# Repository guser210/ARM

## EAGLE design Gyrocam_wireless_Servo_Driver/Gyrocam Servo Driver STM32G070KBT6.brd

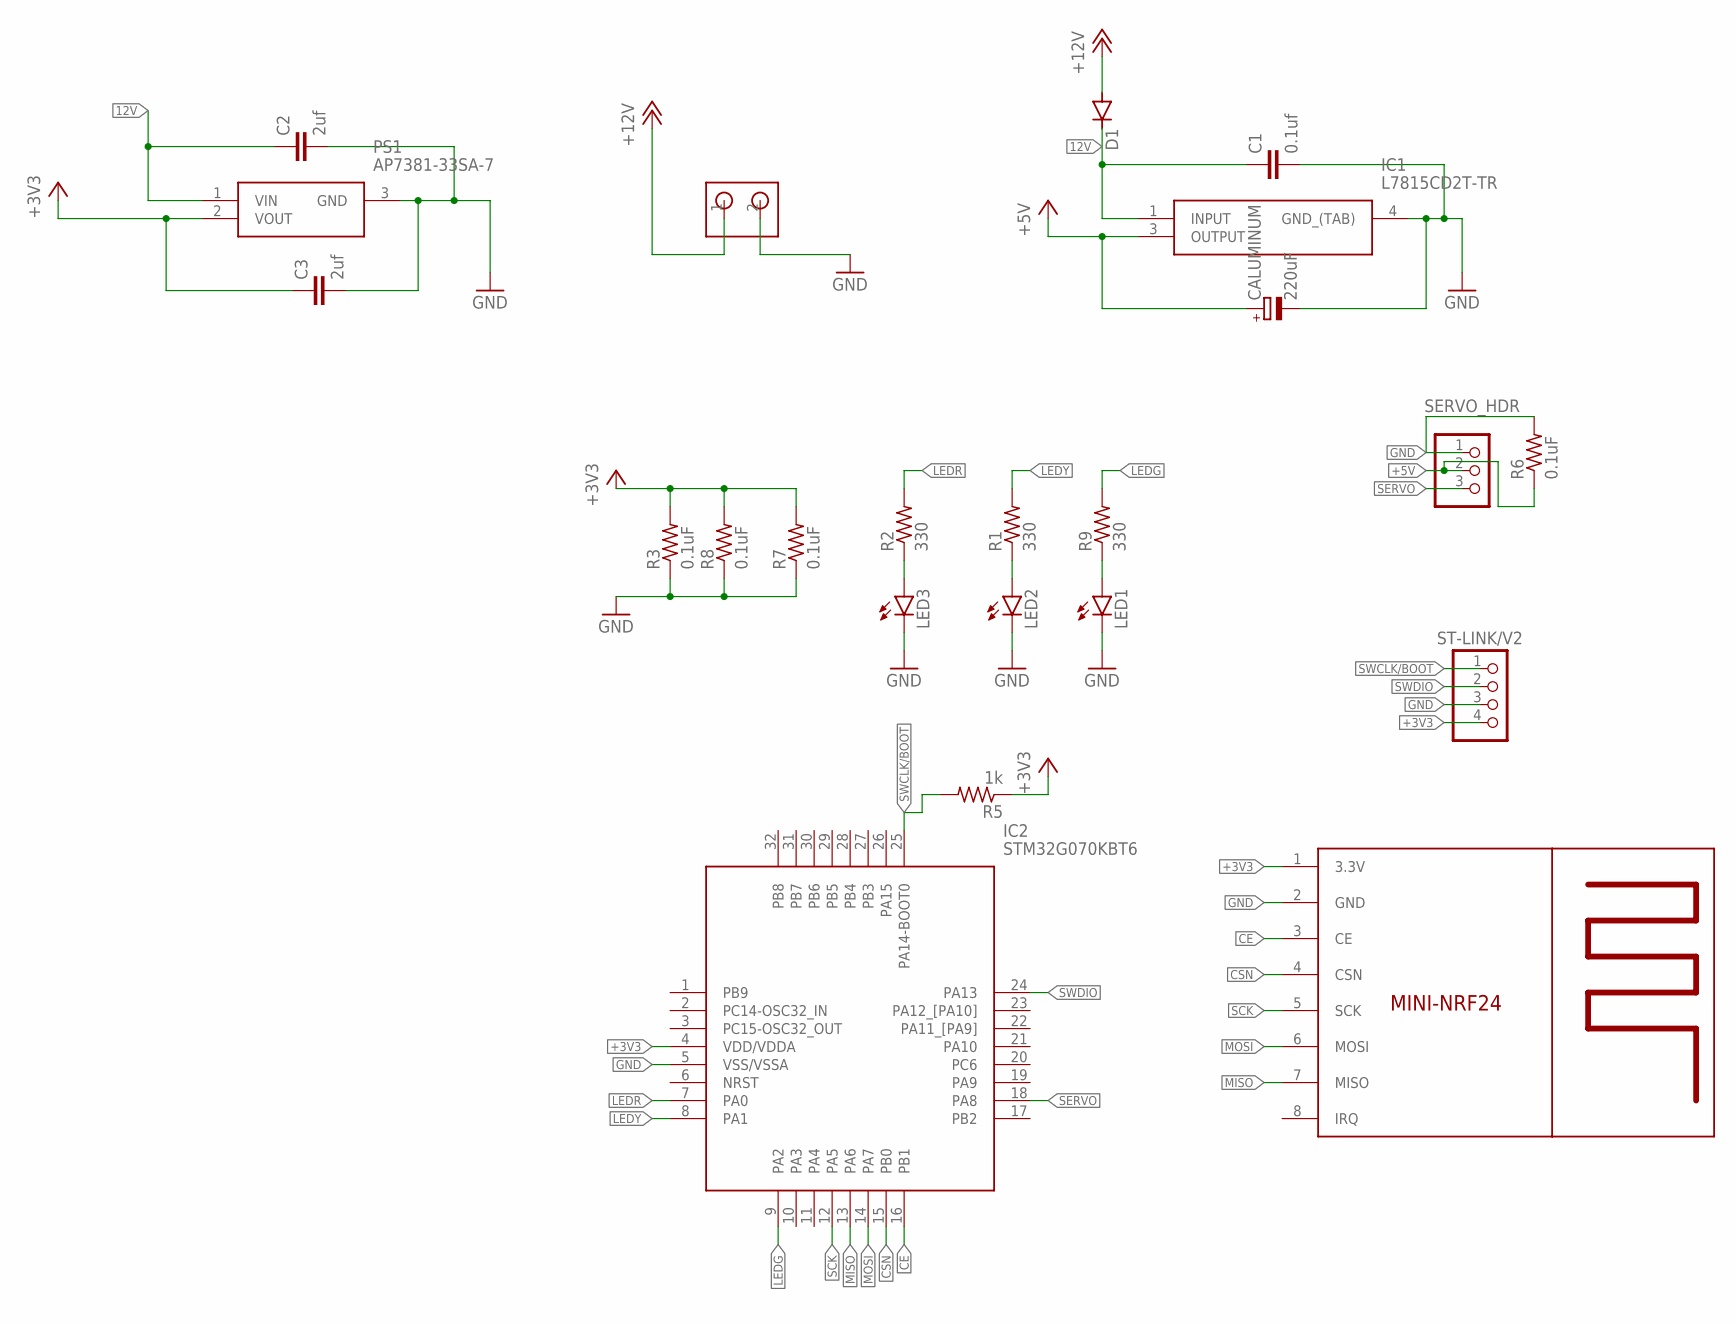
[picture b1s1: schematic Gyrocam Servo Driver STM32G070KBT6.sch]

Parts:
C1: 0.1uf; C0805K
C2, C3: 2uf; C0805K
CALUMINUM: 220uF; 153CLV-0810
D1: DIODE-DO-214AC; DO-214AC
IC1: L7815CD2T-TR; TO254P1542X460-3N
IC2: STM32G070KBT6; QFP80P900X900X160-32N
LED1, LED2, LED3: LEDSML0805; SML0805
PS1: AP7381-33SA-7; SOT96P240X120-3N
R1, R2, R9: 330; R0805
R3, R6, R7, R8: 0.1uF; R0805
R5: 1k; R0805
SERVO_HDR: PINHD-1X3; 1X03
ST-LINK/V2: PINHD-1X4; 1X04
U$2: MINI-NRF24L01PSMD; NRF24L01_SMD
U$5: PINHEAD2_18AAWG; PINHEAD2_18AWG

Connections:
12V: C1.1, C2.1, D1.C, IC1.1 (INPUT), PS1.1 (VIN)
+3V3: C3.1, IC2.4 (VDD/VDDA), PS1.2 (VOUT), R3.2, R5.1, R7.2, R8.2, ST-LINK/V2.4, U$2.1 (3.3V)
+5V: CALUMINUM.+, IC1.3 (OUTPUT), R6.1, SERVO_HDR.2
+12V: D1.A, U$5.1
CE: IC2.16 (PB1), U$2.3 (CE)
CSN: IC2.15 (PB0), U$2.4 (CSN)
GND: C1.2, C2.2, C3.2, CALUMINUM.-, IC1.4 (GND_(TAB)), IC2.5 (VSS/VSSA), LED1.C, LED2.C, LED3.C, PS1.3 (GND), R3.1, R6.2, R7.1, R8.1, SERVO_HDR.1, ST-LINK/V2.3, U$2.2 (GND), U$5.2
LEDG: IC2.9 (PA2), R9.2
LEDR: IC2.7 (PA0), R2.2
LEDY: IC2.8 (PA1), R1.2
MISO: IC2.13 (PA6), U$2.7 (MISO)
MOSI: IC2.14 (PA7), U$2.6 (MOSI)
unnamed: LED2.A, R1.1
unnamed: LED3.A, R2.1
unnamed: LED1.A, R9.1
SCK: IC2.12 (PA5), U$2.5 (SCK)
SERVO: IC2.18 (PA8), SERVO_HDR.3
SWCLK/BOOT: IC2.25 (PA14-BOOT0), R5.2, ST-LINK/V2.1
SWDIO: IC2.24 (PA13), ST-LINK/V2.2

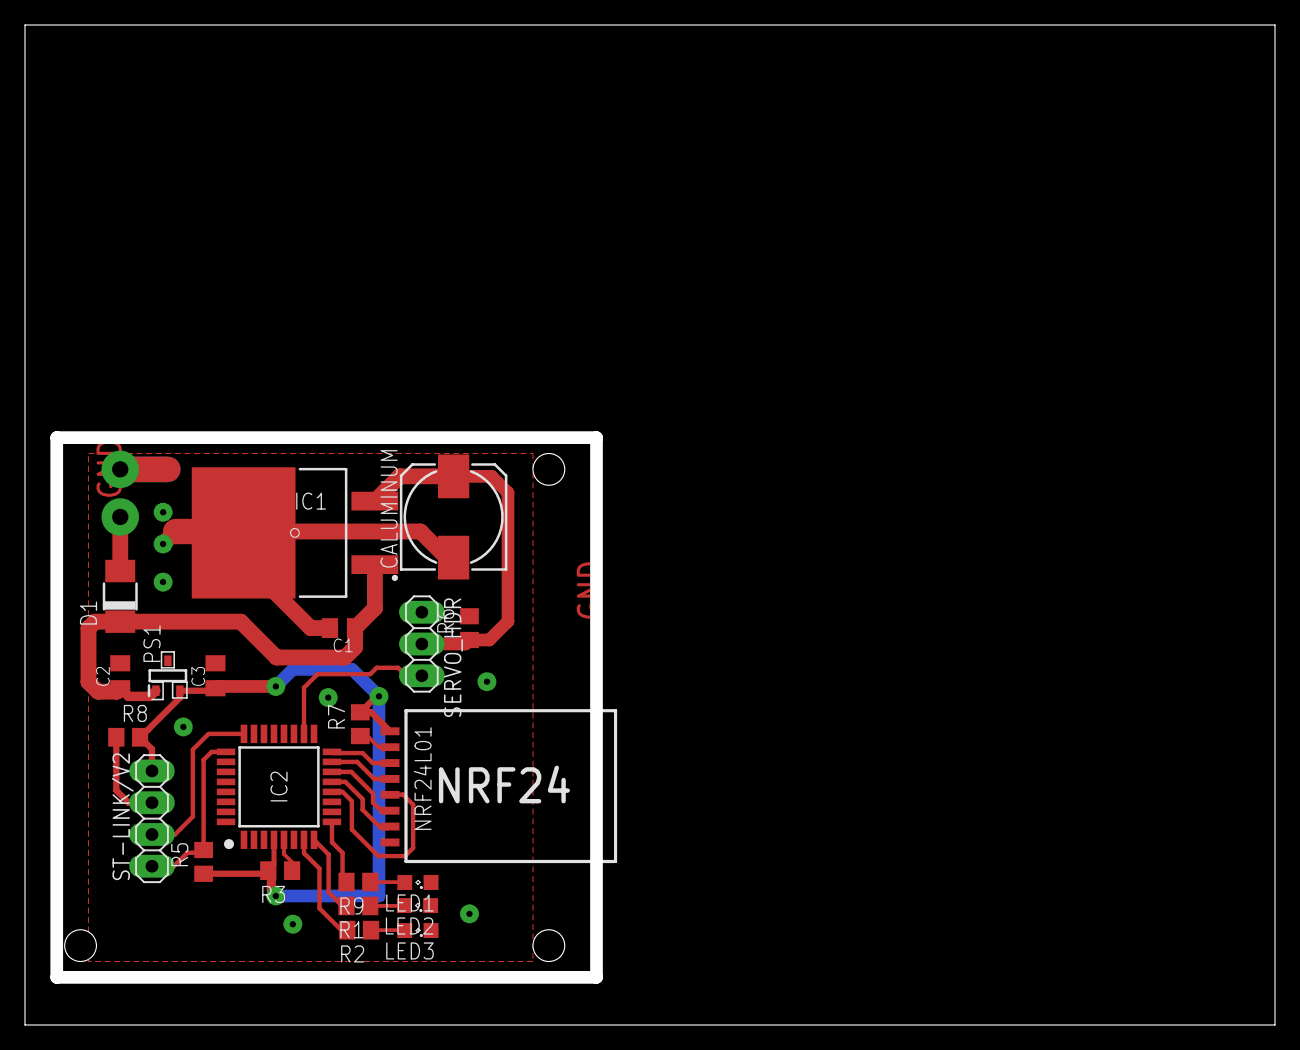
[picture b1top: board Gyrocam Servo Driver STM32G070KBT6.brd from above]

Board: 2 copper layers, 99.0 x 79.0 mm, 23 parts (0 on the bottom side), 19 nets.

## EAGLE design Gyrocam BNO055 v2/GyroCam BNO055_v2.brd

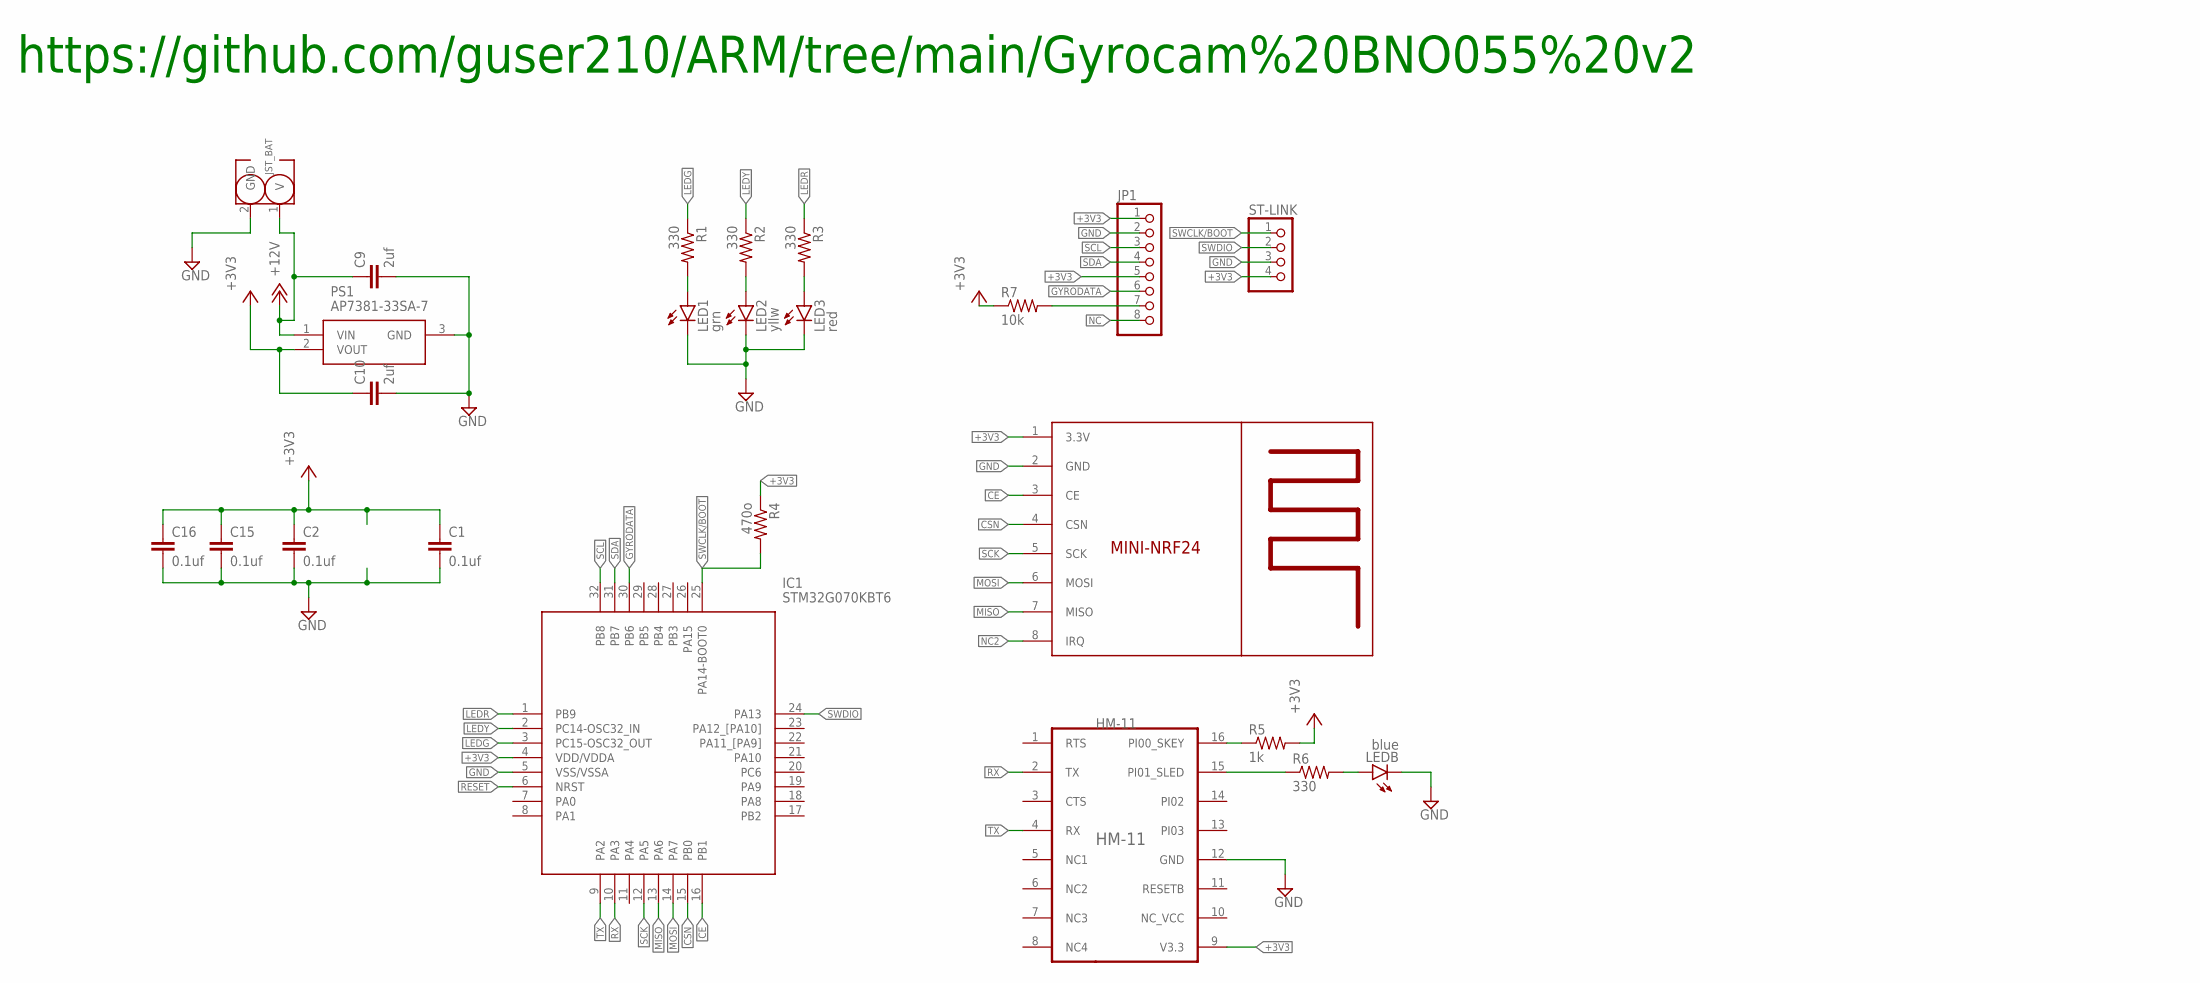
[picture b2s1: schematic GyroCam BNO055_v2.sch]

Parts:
C1: 0.1uf; C0603K
C2, C15, C16: 0.1uf; C0805K
C9, C10: 2uf; C0805K
IC1: STM32G070KBT6; QFP80P900X900X160-32N
JP1: PINHD-1X8; 1X08
LED1: grn; SML0805
LED2: yllw; SML0805
LED3: red; SML0805
LEDB: blue; SML0805
PS1: AP7381-33SA-7; SOT96P240X120-3N
R1, R2, R3, R6: 330; M0805
R4: 470o; M0805
R5: 1k; M0805
R7: 10k; M0805
ST-LINK: PINHD-1X4; 1X04
SUPP: JST2.0MM_2PIN
U$1: HM-11
U$3: NRF24; NRF24L01_SMD

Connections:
+3V3: C1.1, C2.1, C10.1, C15.1, C16.1, IC1.4 (VDD/VDDA), JP1.1, JP1.5, PS1.2 (VOUT), R4.1, R5.2, R7.1, ST-LINK.4, U$1.9 (V3.3), U$3.1 (3.3V)
+12V: C9.1, PS1.1 (VIN), SUPP.1 (V)
BOOT: JP1.7, R7.2
CE: IC1.16 (PB1), U$3.3 (CE)
CSN: IC1.15 (PB0), U$3.4 (CSN)
GND: C1.2, C2.2, C9.2, C10.2, C15.2, C16.2, IC1.5 (VSS/VSSA), JP1.2, LED1.C, LED2.C, LED3.C, LEDB.C, PS1.3 (GND), ST-LINK.3, SUPP.2 (GND), U$1.12 (GND), U$3.2 (GND)
GYRODATA: IC1.30 (PB6), JP1.6
LEDG: IC1.3 (PC15-OSC32_OUT), R1.1
LEDR: IC1.1 (PB9), R3.1
LEDY: IC1.2 (PC14-OSC32_IN), R2.1
MISO: IC1.13 (PA6), U$3.7 (MISO)
MOSI: IC1.14 (PA7), U$3.6 (MOSI)
unnamed: LED2.A, R2.2
unnamed: LED1.A, R1.2
unnamed: LED3.A, R3.2
unnamed: R5.1, U$1.16 (PI00_SKEY)
unnamed: R6.1, U$1.15 (PI01_SLED)
unnamed: LEDB.A, R6.2
NC: JP1.8
NC2: U$3.8 (IRQ)
RESET: IC1.6 (NRST)
RX: IC1.10 (PA3), U$1.2 (TX)
SCK: IC1.12 (PA5), U$3.5 (SCK)
SCL: IC1.32 (PB8), JP1.3
SDA: IC1.31 (PB7), JP1.4
SWCLK/BOOT: IC1.25 (PA14-BOOT0), R4.2, ST-LINK.1
SWDIO: IC1.24 (PA13), ST-LINK.2
TX: IC1.9 (PA2), U$1.4 (RX)

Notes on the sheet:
https://github.com/guser210/ARM/tree/main/Gyrocam%20BNO055%20v2

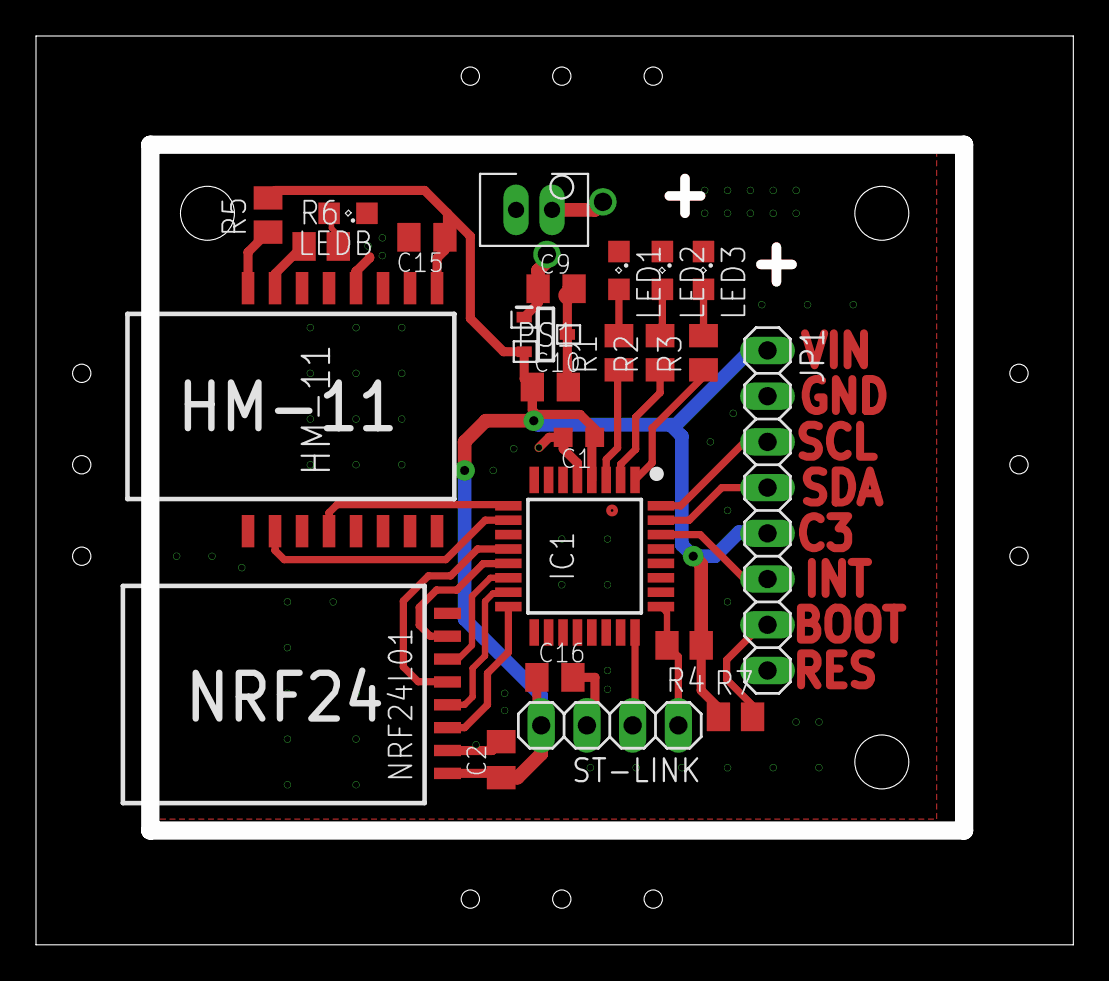
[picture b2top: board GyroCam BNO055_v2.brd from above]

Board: 2 copper layers, 56.6 x 49.5 mm, 24 parts (0 on the bottom side), 25 nets.

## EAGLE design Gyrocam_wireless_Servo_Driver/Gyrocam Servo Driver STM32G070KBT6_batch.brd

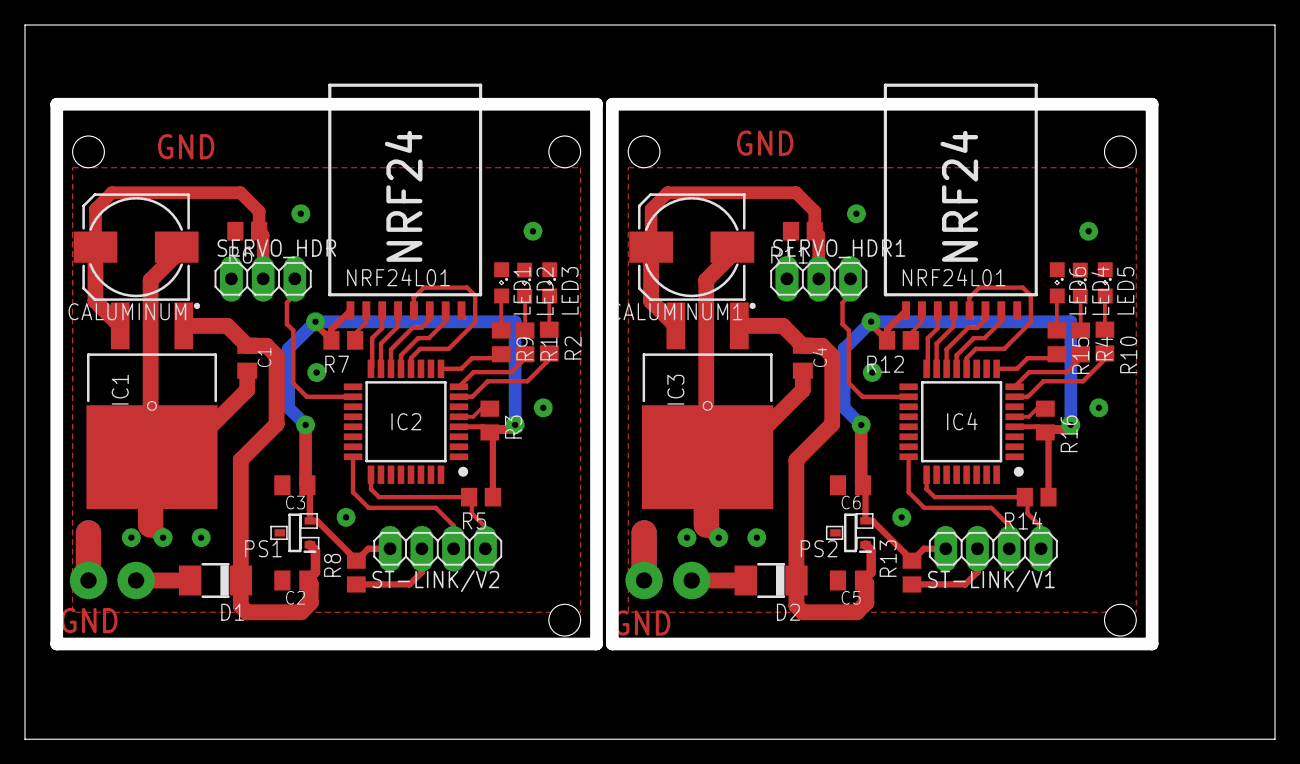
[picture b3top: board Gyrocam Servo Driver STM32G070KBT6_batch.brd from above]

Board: 2 copper layers, 99.0 x 56.1 mm, 46 parts (0 on the bottom side), 38 nets.

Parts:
C1, C4: 0.1uf; C0805K
C2, C3, C5, C6: 2uf; C0805K
CALUMINUM, CALUMINUM1: 220uF; 153CLV-0810
D1, D2: DIODE; DO-214AC
IC1, IC3: L7815CD2T-TR; TO254P1542X460-3N
IC2, IC4: STM32G070KBT6; QFP80P900X900X160-32N
LED1, LED6: LEDG; SML0805
LED2, LED4: LEDY; SML0805
LED3, LED5: LEDR; SML0805
PS1, PS2: AP7381-33SA-7; SOT96P240X120-3N
R1, R2, R4, R9, R10, R15: 330; R0805
R3, R7, R12, R16: .1uF; R0805
R5, R14: 1k; R0805
R6, R8, R11, R13: 0.1uF; R0805
SERVO_HDR, SERVO_HDR1: 1X03
ST-LINK/V1, ST-LINK/V2: 1X04
U$1, U$2: NRF24L01; NRF24L01_SMD
U$3, U$5: PINHEAD2_18AAWG; PINHEAD2_18AWG

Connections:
12V: C1.1, C2.1, D1.C, IC1.1, PS1.1
12V1: C4.1, C5.1, D2.C, IC3.1, PS2.1
+3V1: C6.1, IC4.4, PS2.2, R12.2, R13.2, R14.1, R16.2, ST-LINK/V1.4, U$1.1
+3V3: C3.1, IC2.4, PS1.2, R3.2, R5.1, R7.2, R8.2, ST-LINK/V2.4, U$2.1
+5V: CALUMINUM.+, IC1.3, R6.1, SERVO_HDR.2
+5V1: CALUMINUM1.+, IC3.3, R11.1, SERVO_HDR1.2
+12V: D1.A, U$5.1
+12V1: D2.A, U$3.1
CE: IC2.16, U$2.3
CE1: IC4.16, U$1.3
CSN: IC2.15, U$2.4
CSN1: IC4.15, U$1.4
GND: C1.2, C2.2, C3.2, CALUMINUM.-, IC1.4, IC2.5, LED1.C, LED2.C, LED3.C, PS1.3, R3.1, R6.2, R7.1, R8.1, SERVO_HDR.1, ST-LINK/V2.3, U$2.2, U$5.2
GND1: C4.2, C5.2, C6.2, CALUMINUM1.-, IC3.4, IC4.5, LED4.C, LED5.C, LED6.C, PS2.3, R11.2, R12.1, R13.1, R16.1, SERVO_HDR1.1, ST-LINK/V1.3, U$1.2, U$3.2
LEDG: IC2.9, R9.2
LEDG1: IC4.9, R15.2
LEDR: IC2.7, R2.2
LEDR1: IC4.7, R10.2
LEDY: IC2.8, R1.2
LEDY1: IC4.8, R4.2
MISO: IC2.13, U$2.7
MISO1: IC4.13, U$1.7
MOSI: IC2.14, U$2.6
MOSI1: IC4.14, U$1.6
unnamed: LED2.A, R1.1
unnamed: LED3.A, R2.1
unnamed: LED1.A, R9.1
unnamed: LED4.A, R4.1
unnamed: LED5.A, R10.1
unnamed: LED6.A, R15.1
SCK: IC2.12, U$2.5
SCK1: IC4.12, U$1.5
SERVO: IC2.18, SERVO_HDR.3
SERVO1: IC4.18, SERVO_HDR1.3
SWCLK/BOOT: IC2.25, R5.2, ST-LINK/V2.1
SWCLK/BOOT1: IC4.25, R14.2, ST-LINK/V1.1
SWDIO: IC2.24, ST-LINK/V2.2
SWDIO1: IC4.24, ST-LINK/V1.2

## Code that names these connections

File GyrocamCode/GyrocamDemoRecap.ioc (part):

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Mcu.Name=STM32G070KBTx
Mcu.Package=LQFP32
Mcu.UserName=STM32G070KBTx
PA2.Mode=Asynchronous
PA2.Signal=USART2_TX
PA3.Mode=Asynchronous
PA3.Signal=USART2_RX
PA5.GPIOParameters=GPIO_PuPd
PA5.GPIO_PuPd=GPIO_PULLDOWN
PA5.Mode=Full_Duplex_Master
PA5.Signal=SPI1_SCK
PA6.GPIOParameters=GPIO_PuPd
PA6.GPIO_PuPd=GPIO_PULLDOWN
PA6.Mode=Full_Duplex_Master
PA6.Signal=SPI1_MISO
PA7.GPIOParameters=GPIO_PuPd
PA7.GPIO_PuPd=GPIO_PULLDOWN
PA7.Mode=Full_Duplex_Master
PA7.Signal=SPI1_MOSI
PB0.GPIOParameters=GPIO_Label
PB0.GPIO_Label=CSN
PB0.Signal=GPIO_Output
PB1.GPIOParameters=GPIO_Label
PB1.GPIO_Label=CE
PB1.Signal=GPIO_Output
PB7.Mode=I2C
PB7.Signal=I2C1_SDA
PB8.Mode=I2C
PB8.Signal=I2C1_SCL
PB9.GPIOParameters=GPIO_Label
PB9.GPIO_Label=LEDR
PB9.Signal=GPIO_Output
PC14-OSC32_IN\ (PC14).GPIOParameters=GPIO_Label
PC14-OSC32_IN\ (PC14).GPIO_Label=LEDY
PC14-OSC32_IN\ (PC14).Signal=GPIO_Output
PC15-OSC32_OUT\ (PC15).GPIOParameters=GPIO_Label
PC15-OSC32_OUT\ (PC15).GPIO_Label=LEDG
PC15-OSC32_OUT\ (PC15).Signal=GPIO_Output
RCC.HSE_VALUE=8000000
RCC.SYSCLKFreq_VALUE=64000000
RCC.SYSCLKSource=RCC_SYSCLKSOURCE_PLLCLK
board=custom

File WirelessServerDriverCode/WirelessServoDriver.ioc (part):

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Mcu.Name=STM32G070KBTx
Mcu.Package=LQFP32
Mcu.UserName=STM32G070KBTx
PA0.GPIOParameters=GPIO_Label
PA0.GPIO_Label=LEDR
PA0.Signal=GPIO_Output
PA1.GPIOParameters=GPIO_Label
PA1.GPIO_Label=LEDY
PA1.Signal=GPIO_Output
PA2.GPIOParameters=GPIO_Label
PA2.GPIO_Label=LEDG
PA2.Signal=GPIO_Output
PA5.GPIOParameters=GPIO_PuPd
PA5.GPIO_PuPd=GPIO_PULLDOWN
PA5.Mode=Full_Duplex_Master
PA5.Signal=SPI1_SCK
PA6.GPIOParameters=GPIO_PuPd
PA6.GPIO_PuPd=GPIO_PULLDOWN
PA6.Mode=Full_Duplex_Master
PA6.Signal=SPI1_MISO
PA7.GPIOParameters=GPIO_PuPd
PA7.GPIO_PuPd=GPIO_PULLDOWN
PA7.Mode=Full_Duplex_Master
PA7.Signal=SPI1_MOSI
PA8.Signal=S_TIM1_CH1
PB0.GPIOParameters=GPIO_Label
PB0.GPIO_Label=CSN
PB0.Signal=GPIO_Output
PB1.GPIOParameters=GPIO_Label
PB1.GPIO_Label=CE
PB1.Signal=GPIO_Output
RCC.HSE_VALUE=8000000
RCC.SYSCLKFreq_VALUE=64000000
RCC.SYSCLKSource=RCC_SYSCLKSOURCE_PLLCLK
board=custom
